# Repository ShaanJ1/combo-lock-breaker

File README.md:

# Combo Lock Breaker
This device can cycle through every possible combination on your lock until it finds the correct code, which is then displayed on an LCD screen. In the future this device will also be able to use Samy Kamkar's method to crack locks even faster.
### Highlights
- Fast and Accurate
- Cracks any combination lock in under ____ minutes
- LCD displays the current status, progress, and more
- Quiet & Efficient
### Showcase
*Coming soon...*
### Bill of Materials (BOM)

| **Item Name**                              | **URL**                                                                                                                                                                       | **Price** | **Quantity** | **Per Package** | **Use**                     |
|--------------------------------------------|-------------------------------------------------------------------------------------------------------------------------------------------------------------------------------|-----------|--------------|------------------|----------------------------|
| Power Supply Cable                          | [AliExpress](https://www.aliexpress.com/item/1005007332397741.html)                                                                                                          | $16.96    | 1            | 1                | Power                      |
| Nema 17 Motor                               | [AliExpress](https://www.aliexpress.com/item/32572890101.html?spm=a2g0o.cart.0.0.66ba38daMIFTUY&mp=1)                                                                        | $23.98    | 1            | 1                | Dial turning mechanism     |
| TMC2209                                     | [AliExpress](https://www.aliexpress.com/item/33028050145.html)                                                                                                               | $7.49     | 1            | 3                | Motor driver               |
| Analog Feedback Servo                       | [AliExpress](https://www.aliexpress.com/item/1005007407524023.html)                                                                                                          | $14.81    | 1            | 1                | Shackle opening mechanism  |
| 4x4 Matrix Keypad                           | [AliExpress](https://www.aliexpress.com/item/1005007182495122.html?spm=a2g0o.cart.0.0.56ba38da4Y49U1&mp=1)                                                                   | $2.00     | 1            | 1                | User input                 |
| LCD1602 I2C                                 | [AliExpress](https://www.aliexpress.com/item/1005006151355330.html?spm=a2g0o.cart.0.0.56ba38da4Y49U1&mp=1)                                                                   | $4.13     | 1            | 1                | Displays program output    |
| M3 6mm Screws                               | [AliExpress](https://www.aliexpress.com/item/1005007264845313.html)                                                                                                          | $2.96     | 1            | 50               | Mounting screws            |
| M2.5 10mm Screws                            | [AliExpress](https://www.aliexpress.com/item/1005007264845313.html)                                                                                                          | $2.96     | 1            | 50               | Mounting screws            |
| M2.5 5mm Screws                             | [AliExpress](https://www.aliexpress.com/item/1005007264845313.html)                                                                                                          | $2.96     | 1            | 50               | Mounting screws            |
| M2 5mm Screws                               | [AliExpress](https://www.aliexpress.com/item/1005007264845313.html)                                                                                                          | $2.96     | 1            | 50               | Mounting screws            |
| PCBA                                        | [JLCPCB](https://jlcpcb.com)                                                                                                                                                 | $73.61    | 1            | 5 PCB, 2 PCBA    | Main controller            |
| 1x3 PinHeader                               | [DigiKey](https://www.digikey.ca/en/products/detail/w%C3%BCrth-elektronik/61300311121/4846825)                                                                               | $0.18     | 1            | 1                | Debug connector            |
| 1x4 PinHeader                               | [DigiKey](https://www.digikey.ca/en/products/detail/w%C3%BCrth-elektronik/61300411121/4846827)                                                                               | $0.50     | 3            | 1                | LCD & servo connectors     |
| 1x8 PinHeader                               | [DigiKey](https://www.digikey.ca/en/products/detail/w%C3%BCrth-elektronik/61300811121/4846839)                                                                               | $0.54     | 1            | 1                | Keypad connector           |
| Barrel Jack                                 | [DigiKey](https://www.digikey.ca/en/products/detail/switchcraft-inc/RAPC712BKZ/9997462)                                                                                      | $4.41     | 1            | 1                | Power connector            |

**Total (CAD):** $165.79

**Total (USD):** $117.67

### Images
Schematic

PCB

Main Assembly

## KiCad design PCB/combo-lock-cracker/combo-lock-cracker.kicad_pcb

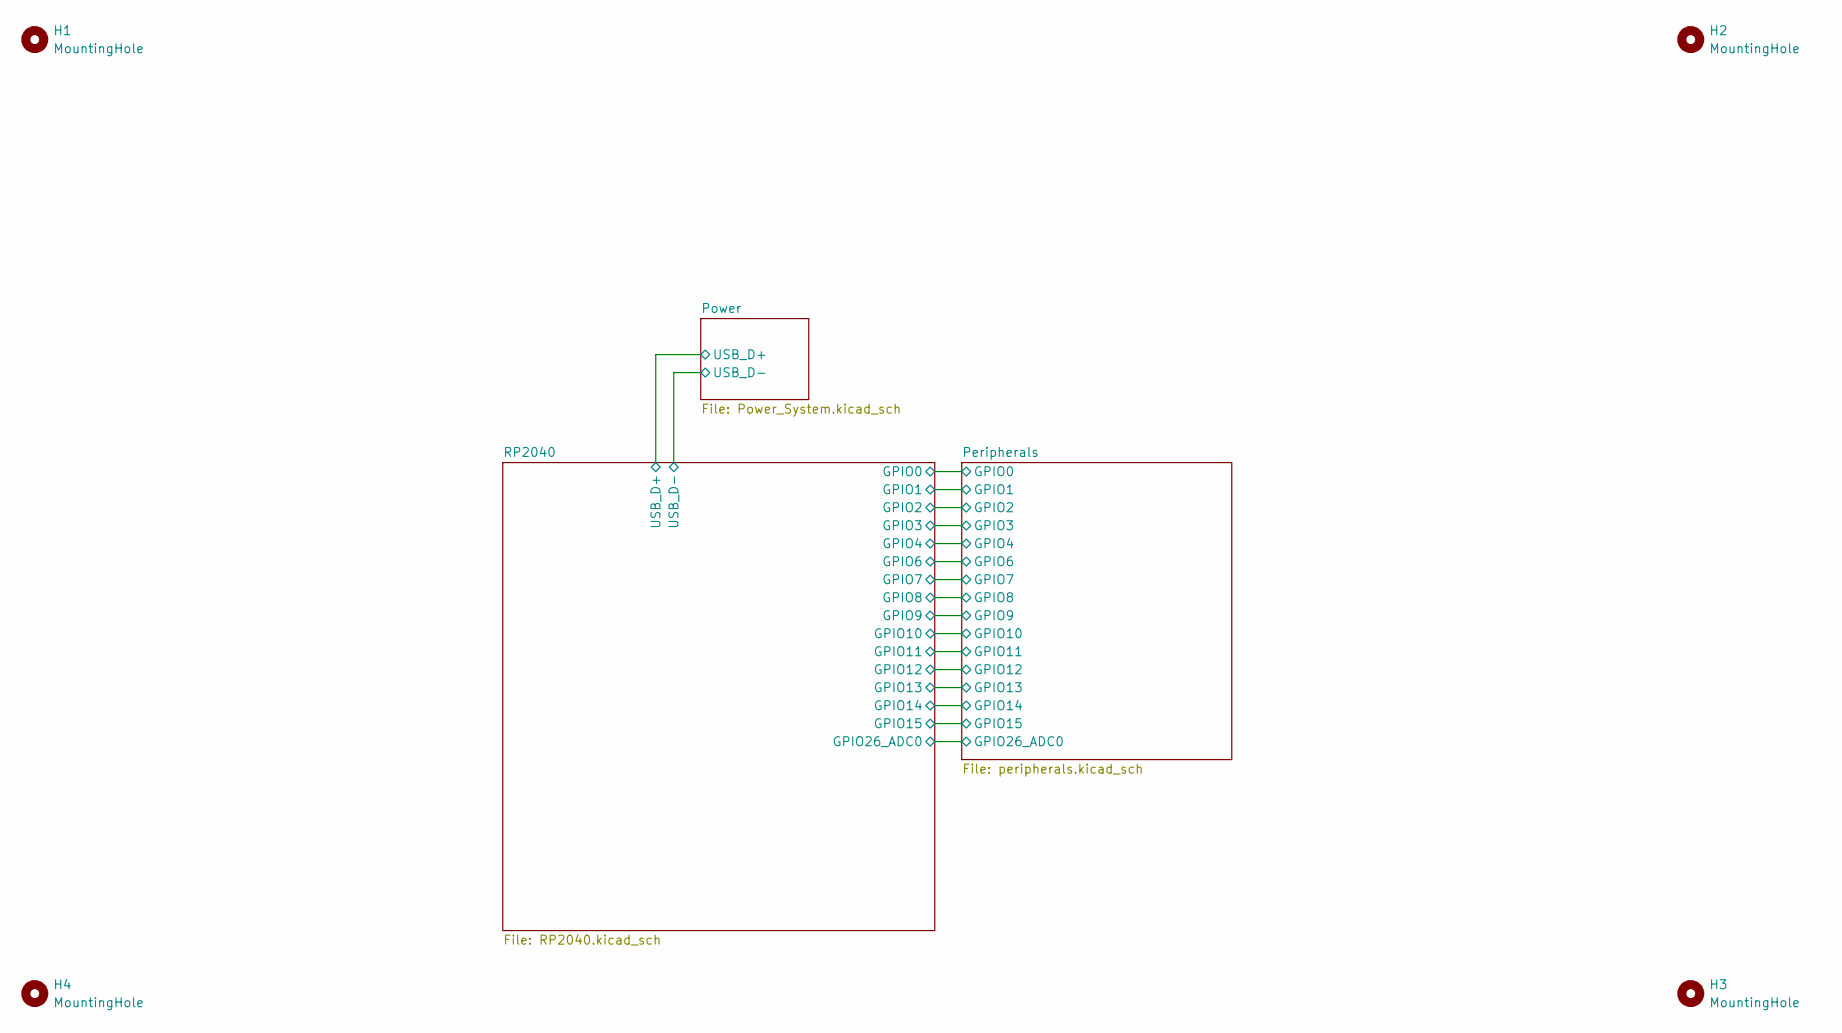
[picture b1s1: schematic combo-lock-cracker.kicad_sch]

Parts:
H1, H2, H3, H4: MountingHole; MountingHole_2.2mm_M2

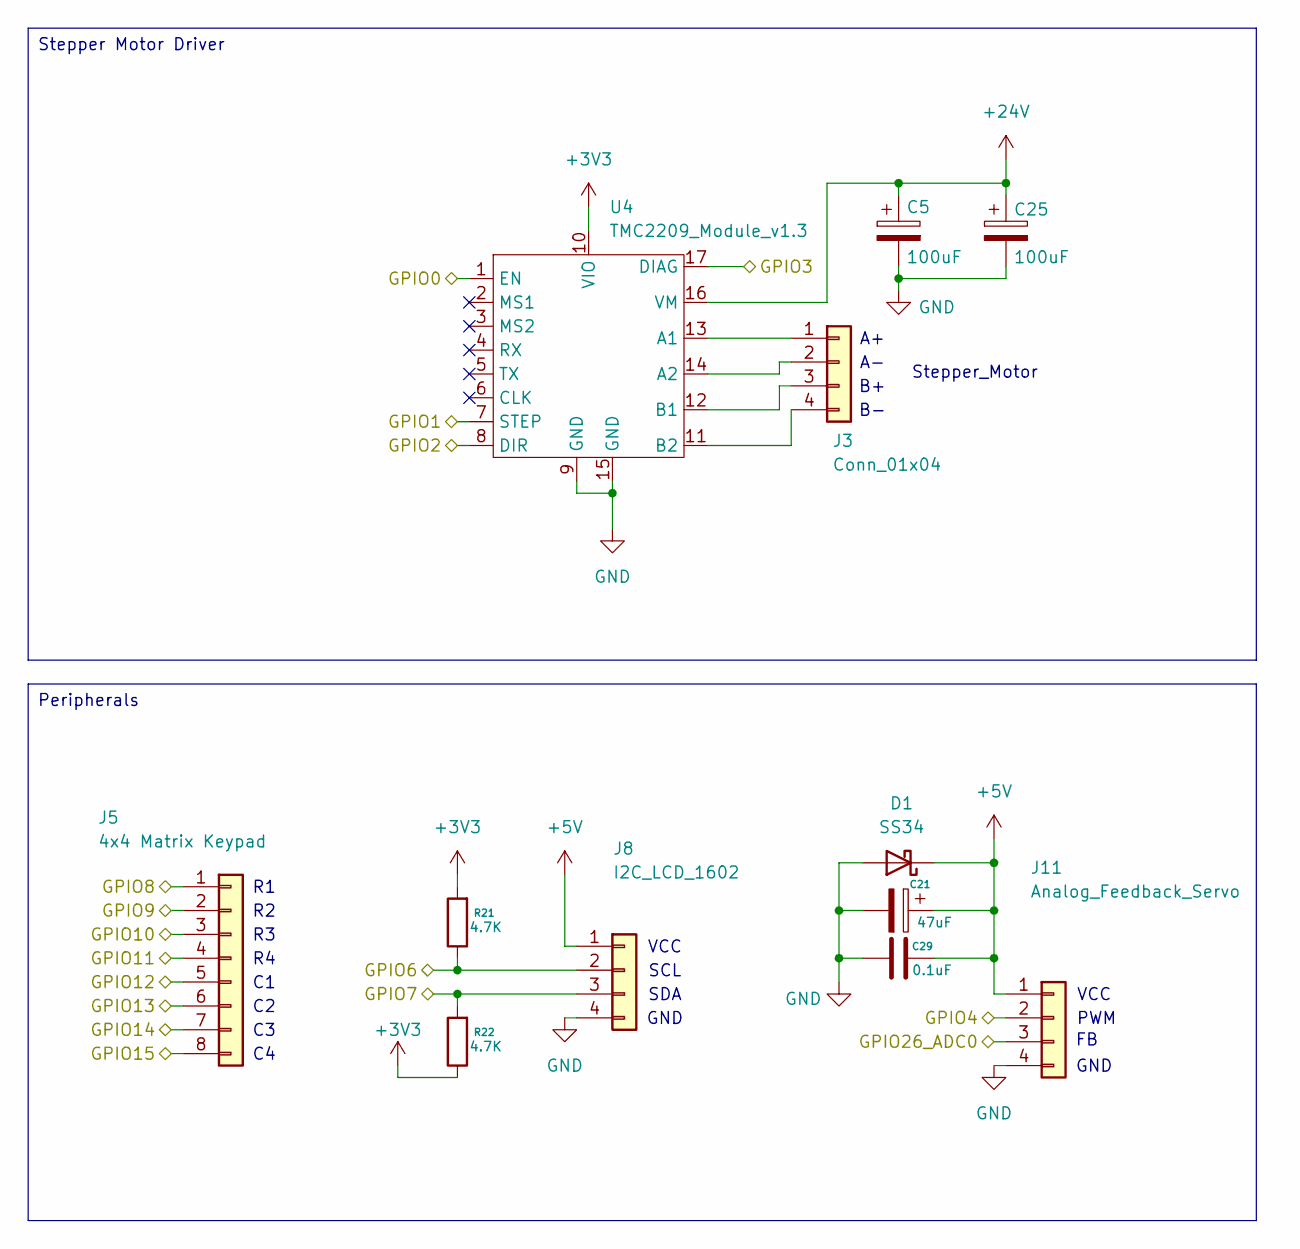
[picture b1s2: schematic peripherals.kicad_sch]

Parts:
C5, C25: 100uF; CP_Elec_6.3x7.7
C21: 47uF; C_0805_2012Metric
C29: 0.1uF; C_0402_1005Metric
D1: SS34; D_SMA
J3: Conn_01x04; PinHeader_1x04_P2.54mm_Vertical
J5: 4x4 Matrix Keypad; PinHeader_1x08_P2.54mm_Vertical
J8: I2C_LCD_1602; PinHeader_1x04_P2.54mm_Vertical
J11: Analog_Feedback_Servo; PinHeader_1x04_P2.54mm_Vertical
R21, R22: 4.7K; R_0402_1005Metric
U4: TMC2209_Module_v1.3; TMC2209

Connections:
+3V3: R21.2, R22.1, U4.10 (VIO); also elsewhere on the board
+5V: C21.1, C29.2, D1.1 (K), J8.1, J11.1; also elsewhere on the board
+24V: C5.1, C25.1, U4.16 (VM); also elsewhere on the board
/Peripherals/GPIO0: U4.1 (EN); also elsewhere on the board
/Peripherals/GPIO1: U4.7 (STEP); also elsewhere on the board
/Peripherals/GPIO2: U4.8 (DIR); also elsewhere on the board
/Peripherals/GPIO3: U4.17 (DIAG); also elsewhere on the board
/Peripherals/GPIO4: J11.2; also elsewhere on the board
/Peripherals/GPIO6: J8.2, R21.1; also elsewhere on the board
/Peripherals/GPIO7: J8.3, R22.2; also elsewhere on the board
/Peripherals/GPIO8: J5.1; also elsewhere on the board
/Peripherals/GPIO9: J5.2; also elsewhere on the board
/Peripherals/GPIO10: J5.3; also elsewhere on the board
/Peripherals/GPIO11: J5.4; also elsewhere on the board
/Peripherals/GPIO12: J5.5; also elsewhere on the board
/Peripherals/GPIO13: J5.6; also elsewhere on the board
/Peripherals/GPIO14: J5.7; also elsewhere on the board
/Peripherals/GPIO15: J5.8; also elsewhere on the board
/Peripherals/GPIO26_ADC0: J11.3; also elsewhere on the board
GND: C5.2, C21.2, C25.2, C29.1, D1.2 (A), J8.4, J11.4, U4.9 (GND), U4.15 (GND); also elsewhere on the board
unnamed: J3.1, U4.13 (A1)
unnamed: J3.2, U4.14 (A2)
unnamed: J3.3, U4.12 (B1)
unnamed: J3.4, U4.11 (B2)

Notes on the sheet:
VCC
SDA
GND
SCL
PWM
Stepper_Motor
Peripherals
Stepper Motor Driver

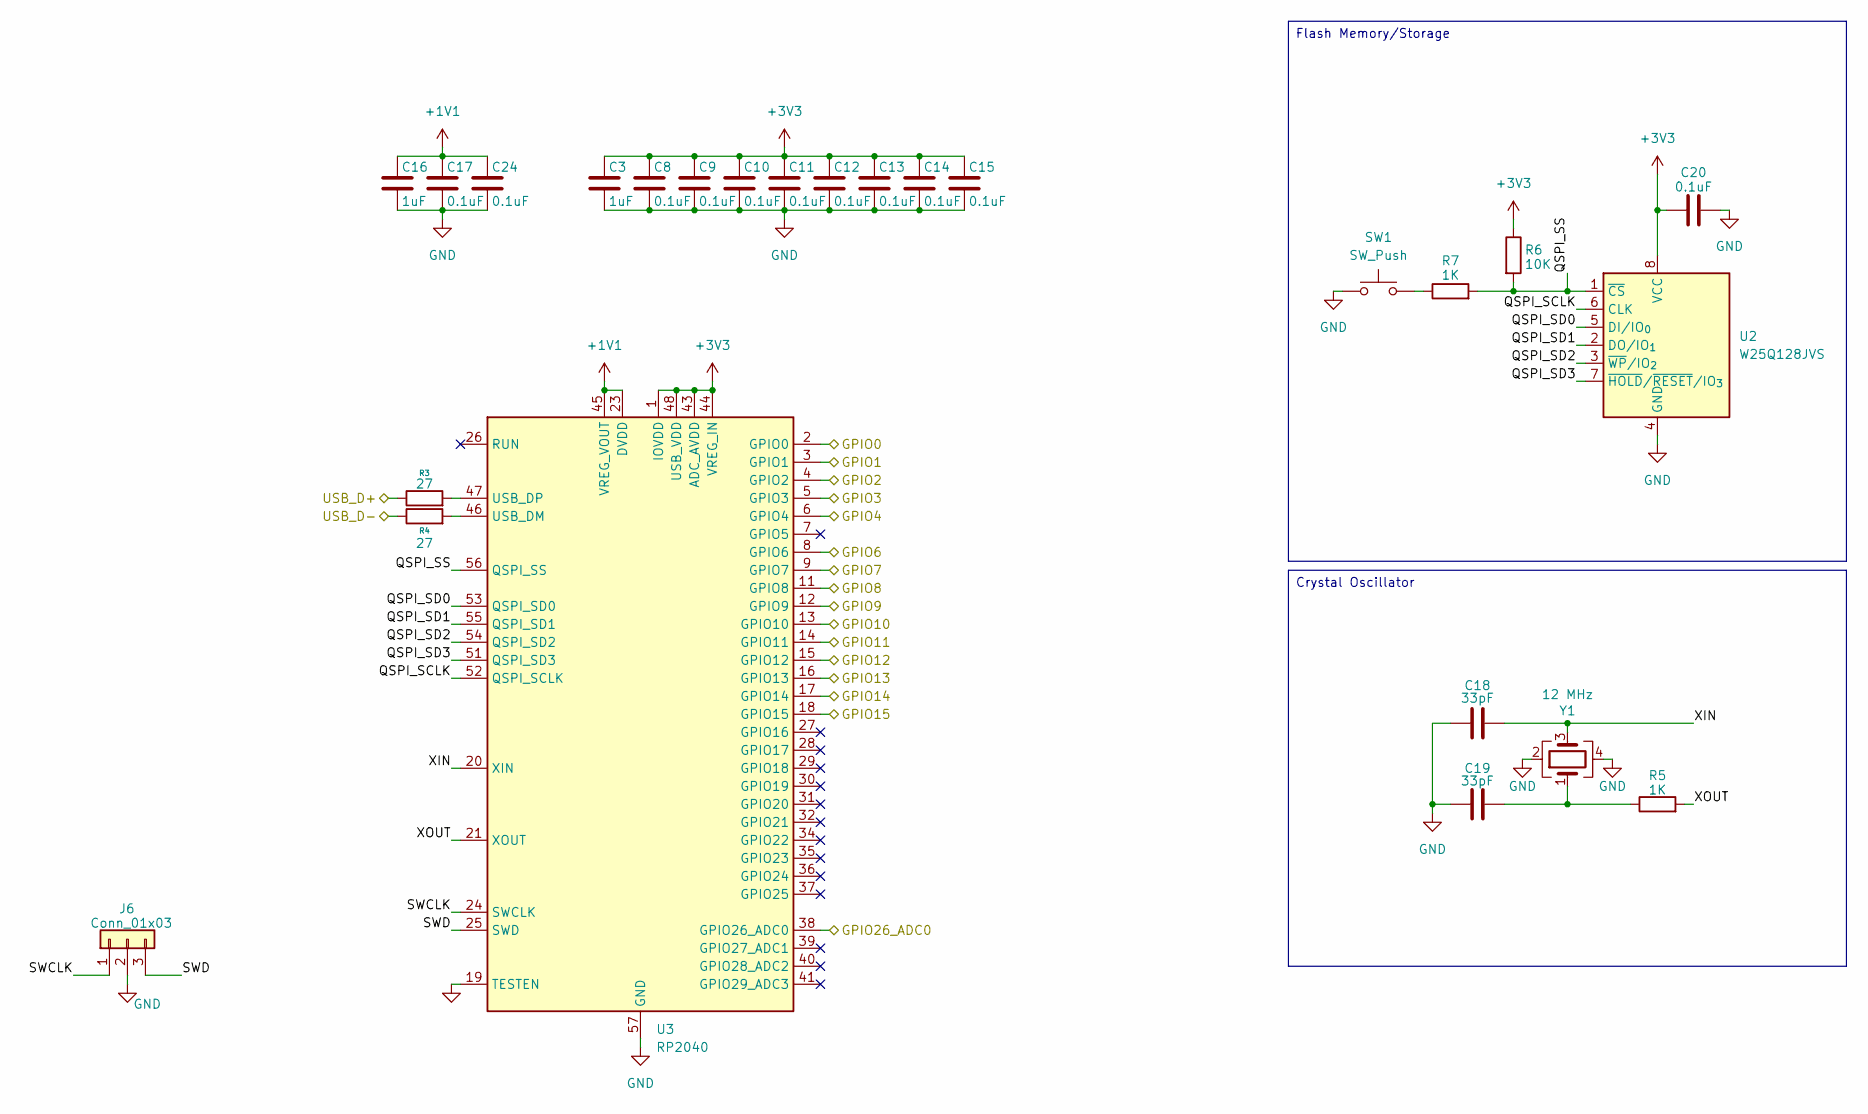
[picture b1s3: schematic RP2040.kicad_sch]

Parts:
C3, C16: 1uF; C_0402_1005Metric
C8, C9, C10, C11, C12, C13, C14, C15, C17, C20, C24: 0.1uF; C_0402_1005Metric
C18, C19: 33pF; C_0402_1005Metric
J6: Conn_01x03; PinHeader_1x03_P2.54mm_Vertical
R3, R4: 27; R_0402_1005Metric
R5, R7: 1K; R_0402_1005Metric
R6: 10K; R_0402_1005Metric
SW1: SW_Push; SW_Push_SPST_NO_Alps_SKRK
U2: W25Q128JVS; SOIC-8_5.3x5.3mm_P1.27mm
U3: RP2040; QFN-56-1EP_7x7mm_P0.4mm_EP3.2x3.2mm
Y1: 12 MHz; Crystal_SMD_3225-4Pin_3.2x2.5mm

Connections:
+1V1: C16.1, C17.1, C24.1, U3.23 (DVDD), U3.45 (VREG_VOUT), U3.50 (DVDD)
+3V3: C3.1, C8.1, C9.1, C10.1, C11.1, C12.1, C13.1, C14.1, C15.1, C20.1, R6.1, U2.8 (VCC), U3.1 (IOVDD), U3.10 (IOVDD), U3.22 (IOVDD), U3.33 (IOVDD), U3.42 (IOVDD), U3.43 (ADC_AVDD), U3.44 (VREG_IN), U3.48 (USB_VDD), U3.49 (IOVDD); also elsewhere on the board
/Peripherals/GPIO0: U3.2 (GPIO0); also elsewhere on the board
/Peripherals/GPIO1: U3.3 (GPIO1); also elsewhere on the board
/Peripherals/GPIO2: U3.4 (GPIO2); also elsewhere on the board
/Peripherals/GPIO3: U3.5 (GPIO3); also elsewhere on the board
/Peripherals/GPIO4: U3.6 (GPIO4); also elsewhere on the board
/Peripherals/GPIO6: U3.8 (GPIO6); also elsewhere on the board
/Peripherals/GPIO7: U3.9 (GPIO7); also elsewhere on the board
/Peripherals/GPIO8: U3.11 (GPIO8); also elsewhere on the board
/Peripherals/GPIO9: U3.12 (GPIO9); also elsewhere on the board
/Peripherals/GPIO10: U3.13 (GPIO10); also elsewhere on the board
/Peripherals/GPIO11: U3.14 (GPIO11); also elsewhere on the board
/Peripherals/GPIO12: U3.15 (GPIO12); also elsewhere on the board
/Peripherals/GPIO13: U3.16 (GPIO13); also elsewhere on the board
/Peripherals/GPIO14: U3.17 (GPIO14); also elsewhere on the board
/Peripherals/GPIO15: U3.18 (GPIO15); also elsewhere on the board
/Peripherals/GPIO26_ADC0: U3.38 (GPIO26_ADC0); also elsewhere on the board
/Power/USB_D+: R3.1; also elsewhere on the board
/Power/USB_D-: R4.1; also elsewhere on the board
/RP2040/QSPI_SCLK: U2.6 (CLK), U3.52 (QSPI_SCLK)
/RP2040/QSPI_SD0: U2.5 (DI/IO_{0}), U3.53 (QSPI_SD0)
/RP2040/QSPI_SD1: U2.2 (DO/IO_{1}), U3.55 (QSPI_SD1)
/RP2040/QSPI_SD2: U2.3 (~WP/IO_{2}), U3.54 (QSPI_SD2)
/RP2040/QSPI_SD3: U2.7 (~HOLD/~RESET/IO_{3}), U3.51 (QSPI_SD3)
/RP2040/QSPI_SS: R6.2, R7.2, U2.1 (~CS), U3.56 (QSPI_SS)
/RP2040/SWCLK: J6.1, U3.24 (SWCLK)
/RP2040/SWD: J6.3, U3.25 (SWD)
/RP2040/XIN: C18.2, U3.20 (XIN), Y1.3
/RP2040/XOUT: R5.2, U3.21 (XOUT)
GND: C3.2, C8.2, C9.2, C10.2, C11.2, C12.2, C13.2, C14.2, C15.2, C16.2, C17.2, C18.1, C19.1, C20.2, C24.2, J6.2, SW1.1, U2.4 (GND), U3.19 (TESTEN), U3.57 (GND), Y1.2, Y1.4; also elsewhere on the board
unnamed: C19.2, R5.1, Y1.1
unnamed: R7.1, SW1.2
unnamed: R4.2, U3.46 (USB_DM)
unnamed: R3.2, U3.47 (USB_DP)

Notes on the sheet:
Crystal Oscillator
Flash Memory/Storage

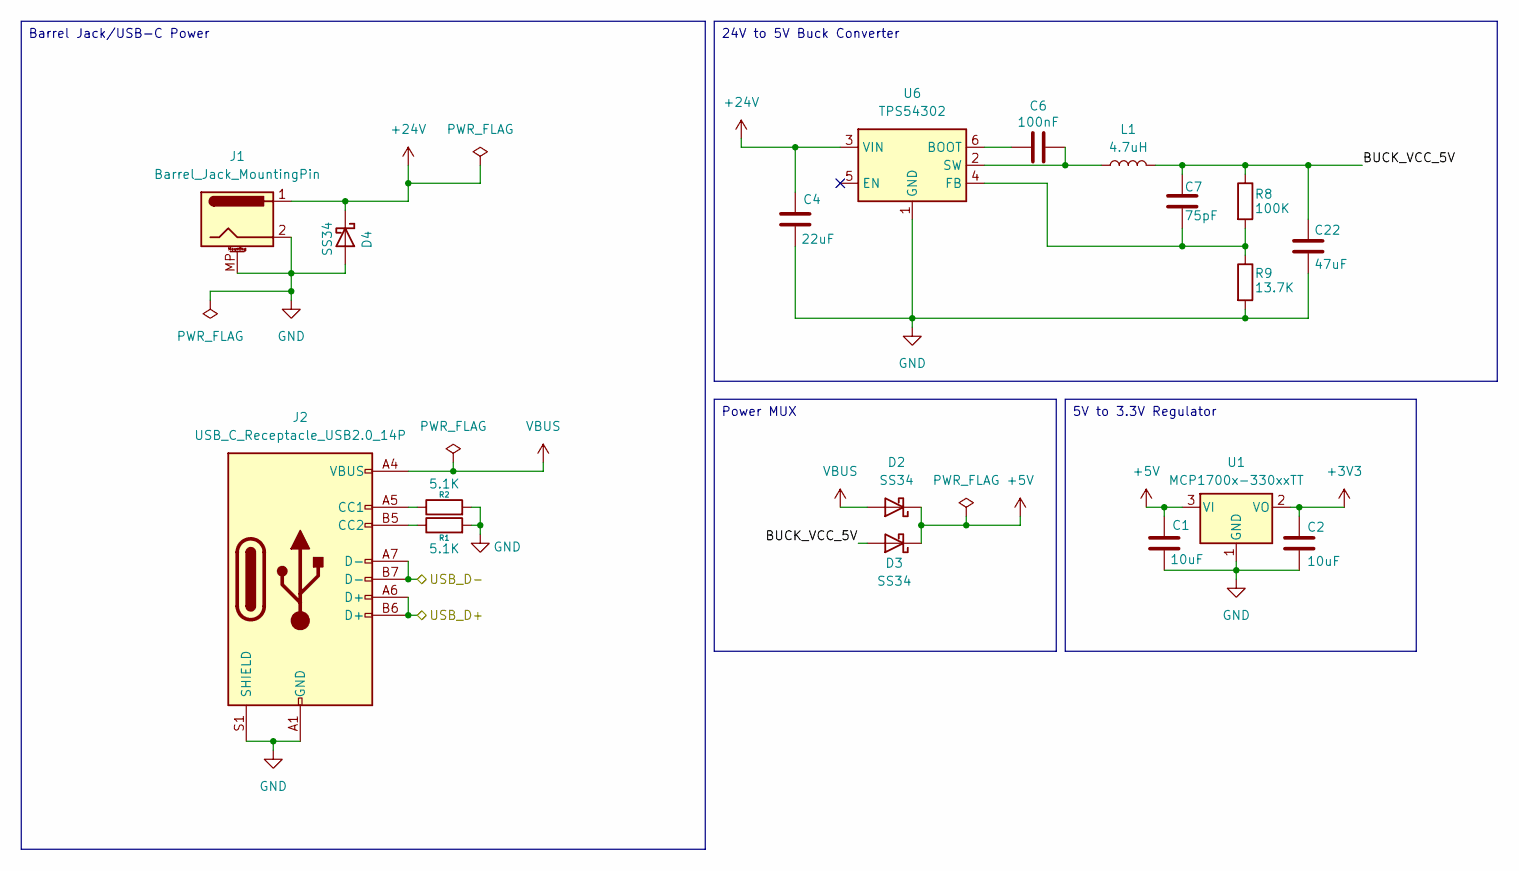
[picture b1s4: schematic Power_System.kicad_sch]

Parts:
C1, C2: 10uF; C_0603_1608Metric
C4: 22uF; C_1206_3216Metric
C6: 100nF; C_0805_2012Metric
C7: 75pF; C_0402_1005Metric
C22: 47uF; C_1206_3216Metric
D2, D3, D4: SS34; D_SMA
J1: Barrel_Jack_MountingPin; BarrelJack_GCT_DCJ200-10-A_Horizontal
J2: USB_C_Receptacle_USB2.0_14P; USB_C_Receptacle_HRO_TYPE-C-31-M-12
L1: 4.7uH; L_7.3x7.3_H3.5
R1, R2: 5.1K; R_0402_1005Metric
R8: 100K; R_0603_1608Metric
R9: 13.7K; R_0603_1608Metric
U1: MCP1700x-330xxTT; SOT-23
U6: TPS54302; SOT-23-6

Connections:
+3V3: C2.1, U1.2 (VO); also elsewhere on the board
+5V: C1.1, D2.1 (K), D3.1 (K), U1.3 (VI); also elsewhere on the board
+24V: C4.1, D4.1 (K), J1.1, U6.3 (VIN); also elsewhere on the board
/Power/BUCK_VCC_5V: C7.1, C22.1, D3.2 (A), L1.2, R8.1
/Power/USB_D+: J2.A6 (D+), J2.B6 (D+); also elsewhere on the board
/Power/USB_D-: J2.A7 (D-), J2.B7 (D-); also elsewhere on the board
GND: C1.2, C2.2, C4.2, C22.2, D4.2 (A), J1.2, J1.MP (MountPin), J2.A1 (GND), J2.A12 (GND), J2.B1 (GND), J2.B12 (GND), J2.S1 (SHIELD), R1.2, R2.2, R9.2, U1.1 (GND), U6.1 (GND); also elsewhere on the board
unnamed: J2.A5 (CC1), R1.1
unnamed: J2.B5 (CC2), R2.1
unnamed: C6.1, U6.6 (BOOT)
unnamed: C7.2, R8.2, R9.1, U6.4 (FB)
unnamed: C6.2, L1.1, U6.2 (SW)
VBUS: D2.2 (A), J2.A4 (VBUS), J2.A9 (VBUS), J2.B4 (VBUS), J2.B9 (VBUS)

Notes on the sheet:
24V to 5V Buck Converter
Barrel Jack/USB-C Power
5V to 3.3V Regulator
Power MUX

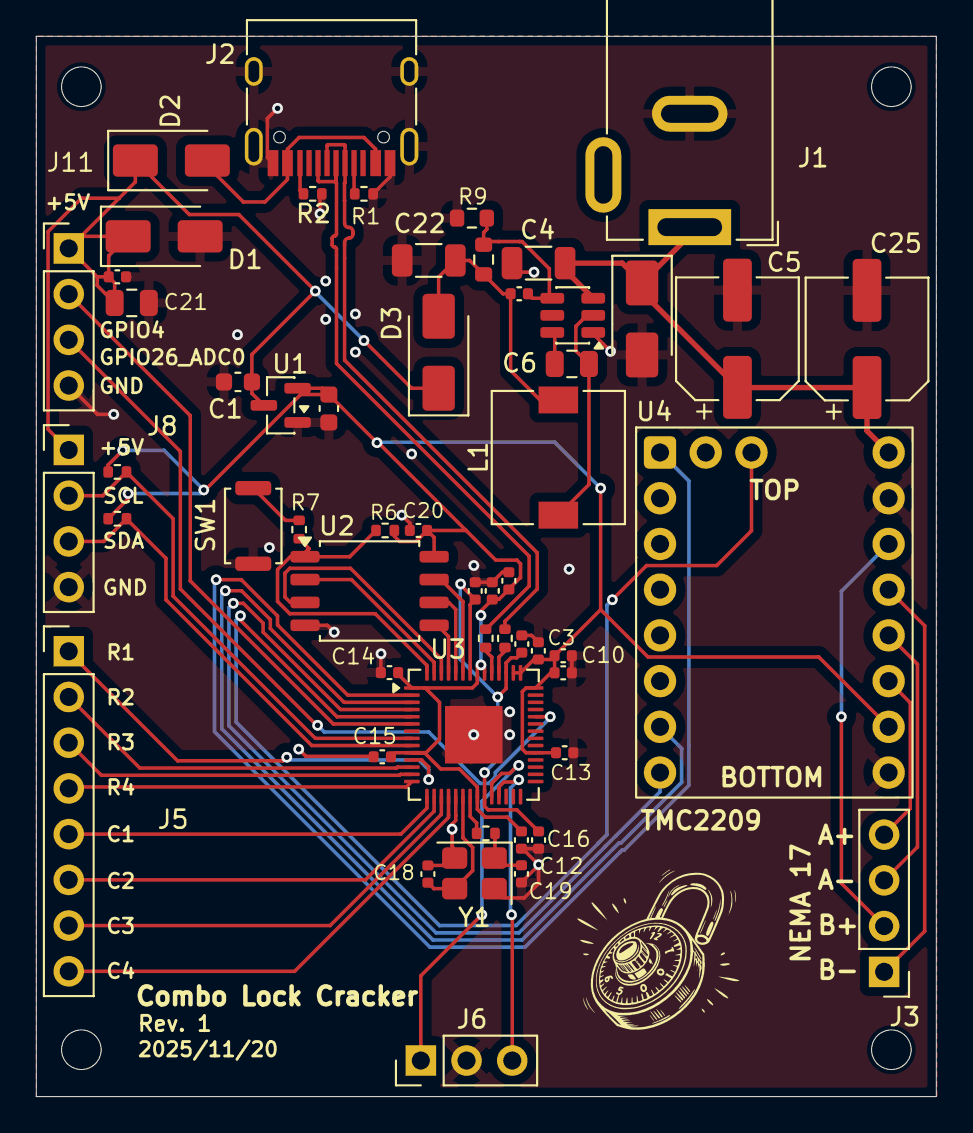
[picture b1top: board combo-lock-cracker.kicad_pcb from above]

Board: 4 copper layers, 50.0 x 58.9 mm, 59 parts (0 on the bottom side), 48 nets.

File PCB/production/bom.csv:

Designator,Footprint,Quantity,Value,LCSC Part #
"C1, C2",0603,2,10uF,
"C10, C11, C12, C13, C14, C15, C17, C20, C24, C29, C8, C9",0402,12,0.1uF,
"C16, C3",0402,2,1uF,
"C18, C19",0402,2,33pF,
C21,0805,1,47uF,
C22,1206,1,47uF,
"C25, C5",CP_Elec_6.3x7.7,2,100uF,
C4,1206,1,22uF,
C6,0805,1,100nF,
C7,0402,1,75pF,
"D1, D2, D3, D4",D_SMA,4,SS34,
J1,BarrelJack_GCT_DCJ200-10-A_Horizontal,1,Barrel_Jack_MountingPin,
J11,PinHeader_1x04_P2.54mm_Vertical,1,Analog_Feedback_Servo,
J2,USB_C_Receptacle_HRO_TYPE-C-31-M-12,1,USB_C_Receptacle_USB2.0_14P,
J3,PinHeader_1x04_P2.54mm_Vertical,1,Conn_01x04,
J4,TMC2209,1,TMC2209_Module_v1.3,
J5,PinHeader_1x08_P2.54mm_Vertical,1,4x4 Matrix Keypad,
J6,PinHeader_1x03_P2.54mm_Vertical,1,Conn_01x03,
J8,PinHeader_1x04_P2.54mm_Vertical,1,I2C_LCD_1602,
L1,L_7.3x7.3_H3.5,1,4.7uH,
"R1, R2",0402,2,5.1K,
"R21, R22",0402,2,4.7K,
"R3, R4",0402,2,27,
"R5, R7",0402,2,1K,
R6,0402,1,10K,
R8,0603,1,100K,
R9,0603,1,13.7K,
SW1,SW_Push_SPST_NO_Alps_SKRK,1,SW_Push,
U1,SOT-23,1,MCP1700x-330xxTT,
U2,SOIC-8_5.3x5.3mm_P1.27mm,1,W25Q128JVS,
U3,QFN-56-1EP_7x7mm_P0.4mm_EP3.2x3.2mm,1,RP2040,
U6,SOT-23-6,1,TPS54302,
Y1,Crystal_SMD_3225-4Pin_3.2x2.5mm,1,12 MHz,

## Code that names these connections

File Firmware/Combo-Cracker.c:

#include <stdio.h>
#include "pico/stdlib.h"
#include "hardware/i2c.h"
#include "hardware/pwm.h"
#include "hardware/uart.h"
#include "hardware/gpio.h"

/* 
 * Hardware: I2C, LCD, Matrix Keypad, Nema 17, TMC2209
 *
 * Pins:
 * - GPIO0: PUL- Stepper Driver
 * - GPIO1: DIR- Stepper Driver
 * - GPIO2: ENA - Stepper Driver
 * - GPIO3: ALM - Stepper Driver Alarm
 * - GPIO4: PWM Analog Feedback Servo
 * - GPIO26_ADC0: FB Analog Feedback Servo 
 * - GPIO6: SCL I2C LCD 1602
 * - GPIO7: SDA I2C LCD 1602
 * - GPIO8: Row 1 Keypad
 * - GPIO9: Row 2 Keypad
 * - GPIO10: Row 3 Keypad
 * - GPIO11: Row 4 Keypad
 * - GPIO12: Column 5 Keypad
 * - GPIO13: Column 6 Keypad
 * - GPIO14: Column 7 Keypad
 * - GPIO15: Column 8 Keypad
*/

// --- Pin Defines ---
// #define STEPPER_PUL_PIN 0
// #define STEPPER_DIR_PIN = 1
// #define STEPPER_ENA_PIN = 2
// #define STEPPER_ALM_PIN = 3

// #define SERVO_PWM_PIN 5
// #define SERVO_FB_PIN 26 // ADC0

// #define LCD_SCL_PIN 6
// #define LCD_SDA_PIN 7

// #define KEYPAD_ROW1_PIN 8
// #define KEYPAD_ROW2_PIN 9
// #define KEYPAD_ROW3_PIN 10
// #define KEYPAD_ROW4_PIN 11
// #define KEYPAD_COLUMN1_PIN 12
// #define KEYPAD_COLUMN2_PIN 13
// #define KEYPAD_COLUMN3_PIN 14
// #define KEYPAD_COLUMN4_PIN 15

// ---------------------------

void initStepper() {

}

void enableDriver() {
    
}

void calibrateStepper() {

}

void set_Stepper_Direction(int dir) {
    
}

void stepper_Pulse_Blocking(int steps, int pulse_delay) { // steps, delay

}

void moveStepperToPositiion(int position) {

}

void turnStepperClockwise(int amount) {
    
}

void stepper_counterclockwise(int amount) {
    
}

void displayToLCD(const char* message) {

}

// After the combination is found, disable the motor, and when it starts back up again, enable it.
// Enabling the motor makes the shaft hold its torque
// Disabling the motor makings the shaft able to free spin by hand

// -------------IMPORTANT NOTES:---------------
//  ENA must be ahead of DIR by at least 200ms. Usually, ENA+ and ENA- are NC(not connected). See“Connector P1 Configurations” for more information. 
//  DIR must be ahead of PUL effective edge by 2us to ensure correct direction;
//  Pulse width not less than 1us;
//  Low level width not less than 1us;
//  Duty cycle of PUL signal is recommended 50%.

double timeTaken = 0;

int main() {
    // Init standard libraries
    stdio_init_all();

    // Initialize hardware pins
    
    
}

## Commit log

2025-11-10 finished
2025-11-10 updated BOM
2025-11-17 BOM changes
    Changed to .csv format
    Found cheaper PSU & analog feedback servo on aliexpress
    Updated Barrel Jack connector to the right one (needed 24v, old one was only up to 20v)
2025-11-22 Switched out Motor & Driver
2025-12-10 actual updated pcb
    uploaded the actual pcb and fixed motor pin wiring
